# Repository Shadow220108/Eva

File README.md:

<h1 align="center">
<br>

<br>
Eva
<br>
</h1>

<h3 align="center">

A heart shaped NFC Hacker Card!  

</h3>
<h4> It uses the NT3H2111W0FHKH NFC chip and also comes with 4 programmable ports to port the card through I2C communciation </h4>  
<div align="center">
   
</div>  

The PCB is 2 layers with dimensions under 100 by 100mm, it is designed to be in a heart shape has some cool silkscreen with black color cause black colored PCBs are cool.    

## Schematics  
Here are the schematics
| Schematics |
| --- |
|    |

## Why was it made?  
It was made for Expedition Ireland! And to give as a gift for my friends :D

## BOM  
|Component|Qty       |Price |Vendor|
|---------|----------|------|------|
|PCB      |5 ( MOQ ) |2$    |JLCPCB|
|PCBA     |2 ( MOQ ) |17.16$|JLCPCB|
|Shipping |          |8.93$ |      |
|Total    |          |28.09$|      |

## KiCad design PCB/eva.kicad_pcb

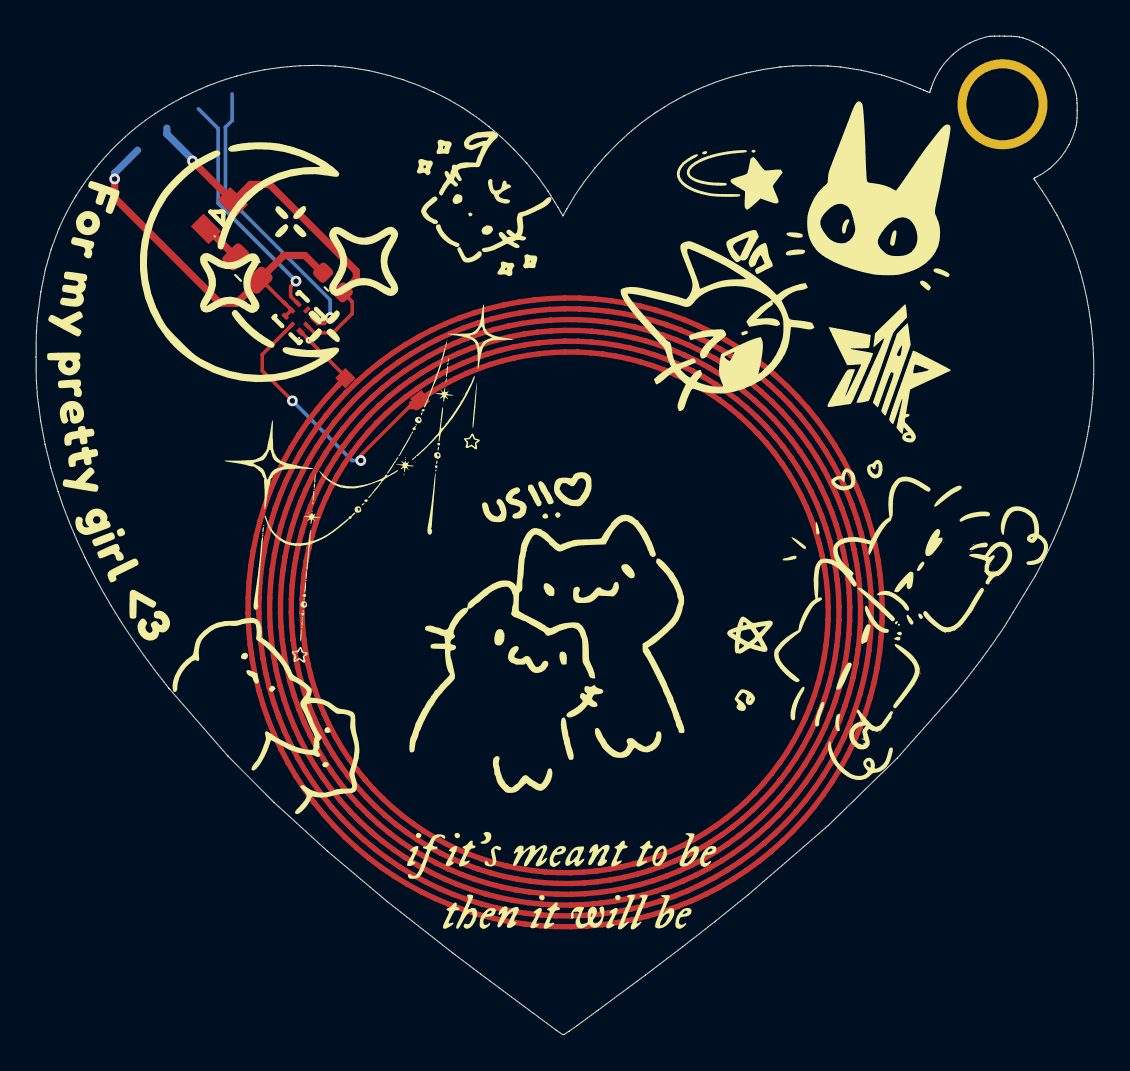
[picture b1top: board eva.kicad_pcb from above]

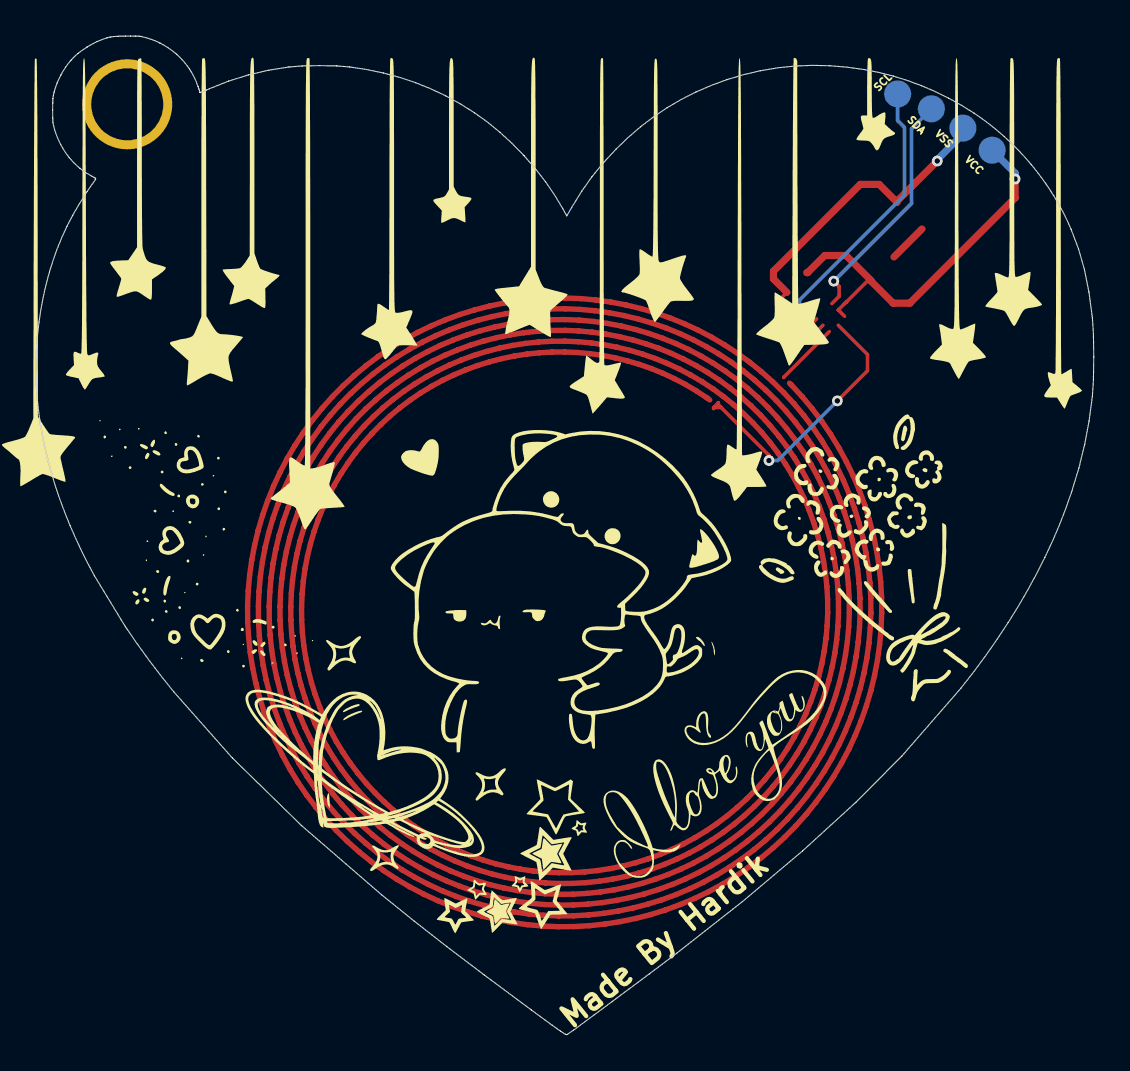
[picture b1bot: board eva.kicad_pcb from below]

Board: 2 copper layers, 58.8 x 55.5 mm, 9 parts (4 on the bottom side), 7 nets.

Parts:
AE1: Antenna_Loop; NFC_36x36_N6_NXP_PN5180
C1: 220nF; C_0603_1608Metric
LED1: 17-21SUYC/TR8; LED0805-R-RD
R1: 47R; R_0805_2012Metric
SCL: TestPoint_Probe; TestPoint_Pad_1.5x1.5mm
TP1: TestPoint_Probe; TestPoint_Pad_1.5x1.5mm
U1: NT3H2111W0FHKH; XQFN-8_L1.6-W1.6-P0.50-BL_NT3H2111W0FHKH
VCC: TestPoint_Probe; TestPoint_Pad_1.5x1.5mm
VSS: TestPoint_Probe; TestPoint_Pad_1.5x1.5mm

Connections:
/SCL: SCL.1 (1_1), U1.3 (SCL)
/SDA: TP1.1 (1_1), U1.5 (SDA)
/VCC: C1.1, R1.2, U1.6 (VCC), U1.7 (VOUT), VCC.1 (1_1)
/VSS: C1.2, LED1.2 (-), U1.2 (VSS), VSS.1 (1_1)
unnamed: LED1.1 (+), R1.1
unnamed: AE1.1, U1.1 (LA)
unnamed: AE1.2, U1.8 (LB)
